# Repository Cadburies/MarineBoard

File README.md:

This project moved into SisuAssistant where the full spec, schematics, and pcb layout are:  https://github.com/Cadburies/SisuAssistant/tree/main/MarineBoard

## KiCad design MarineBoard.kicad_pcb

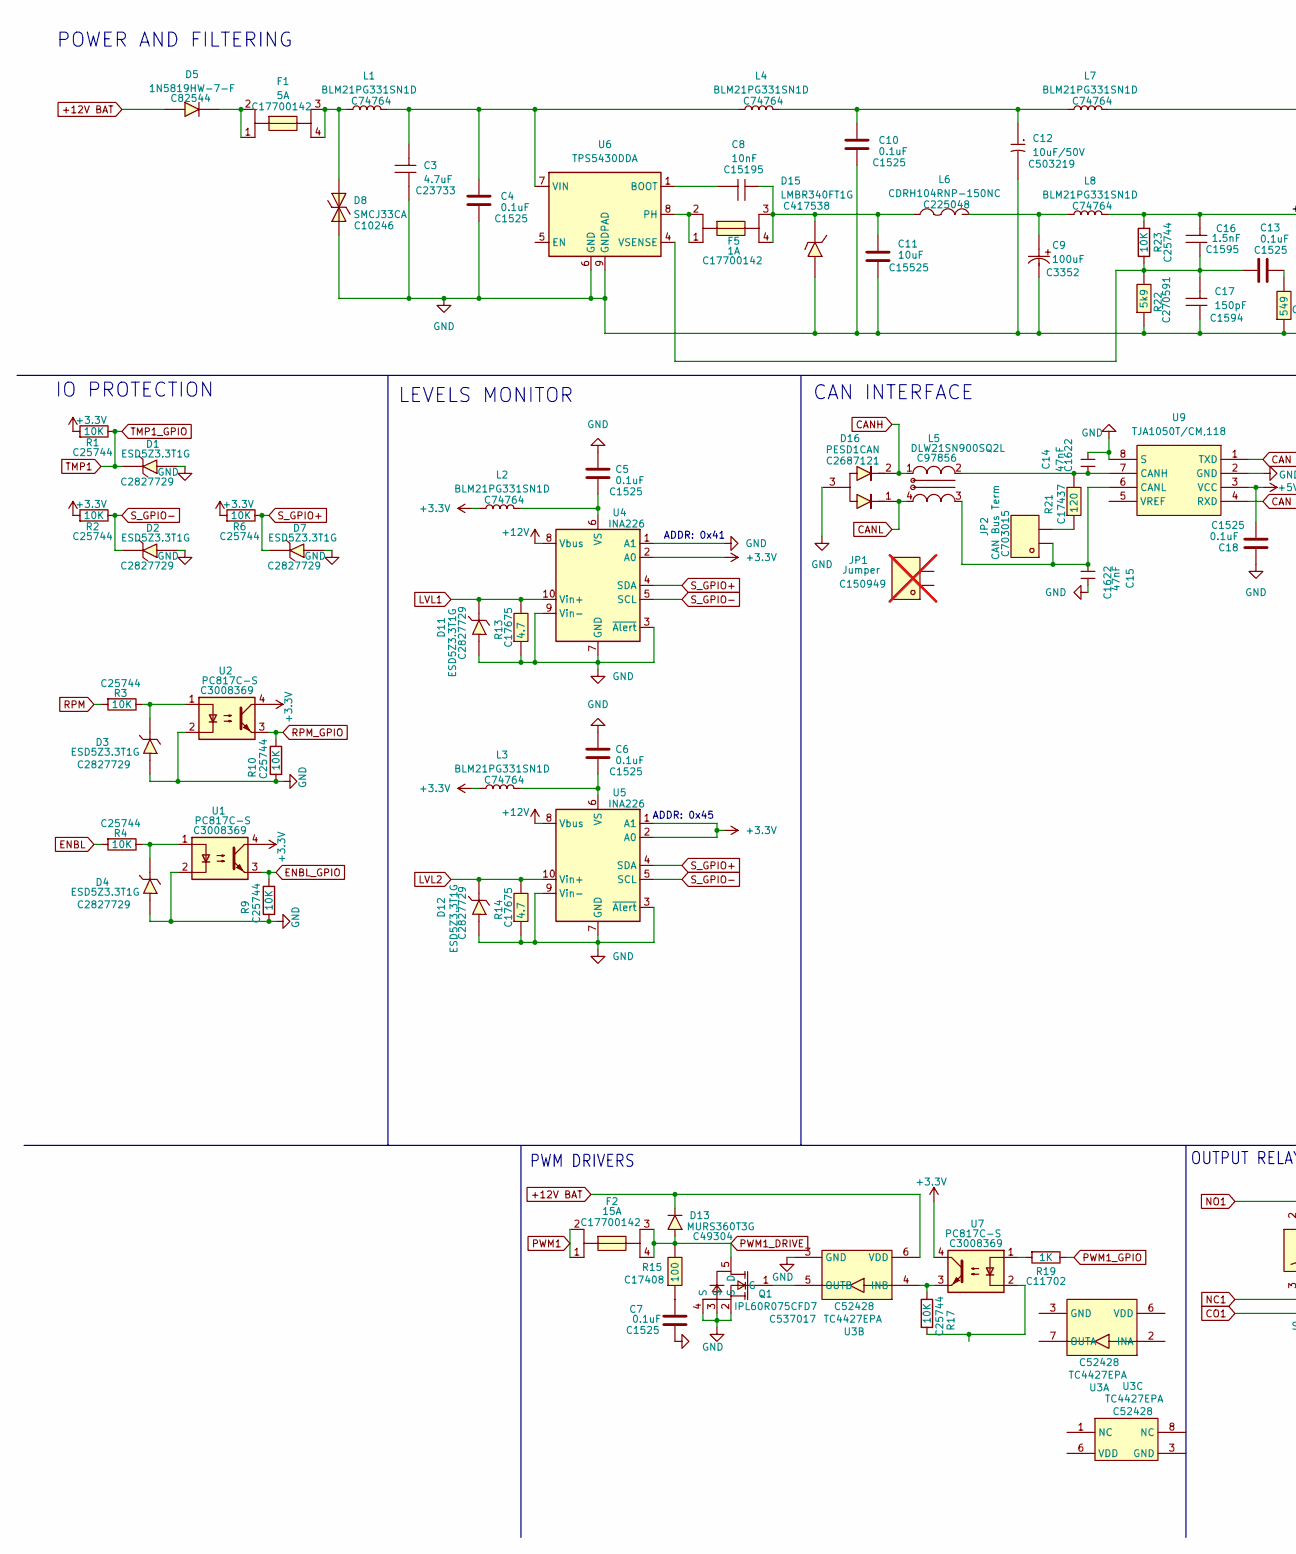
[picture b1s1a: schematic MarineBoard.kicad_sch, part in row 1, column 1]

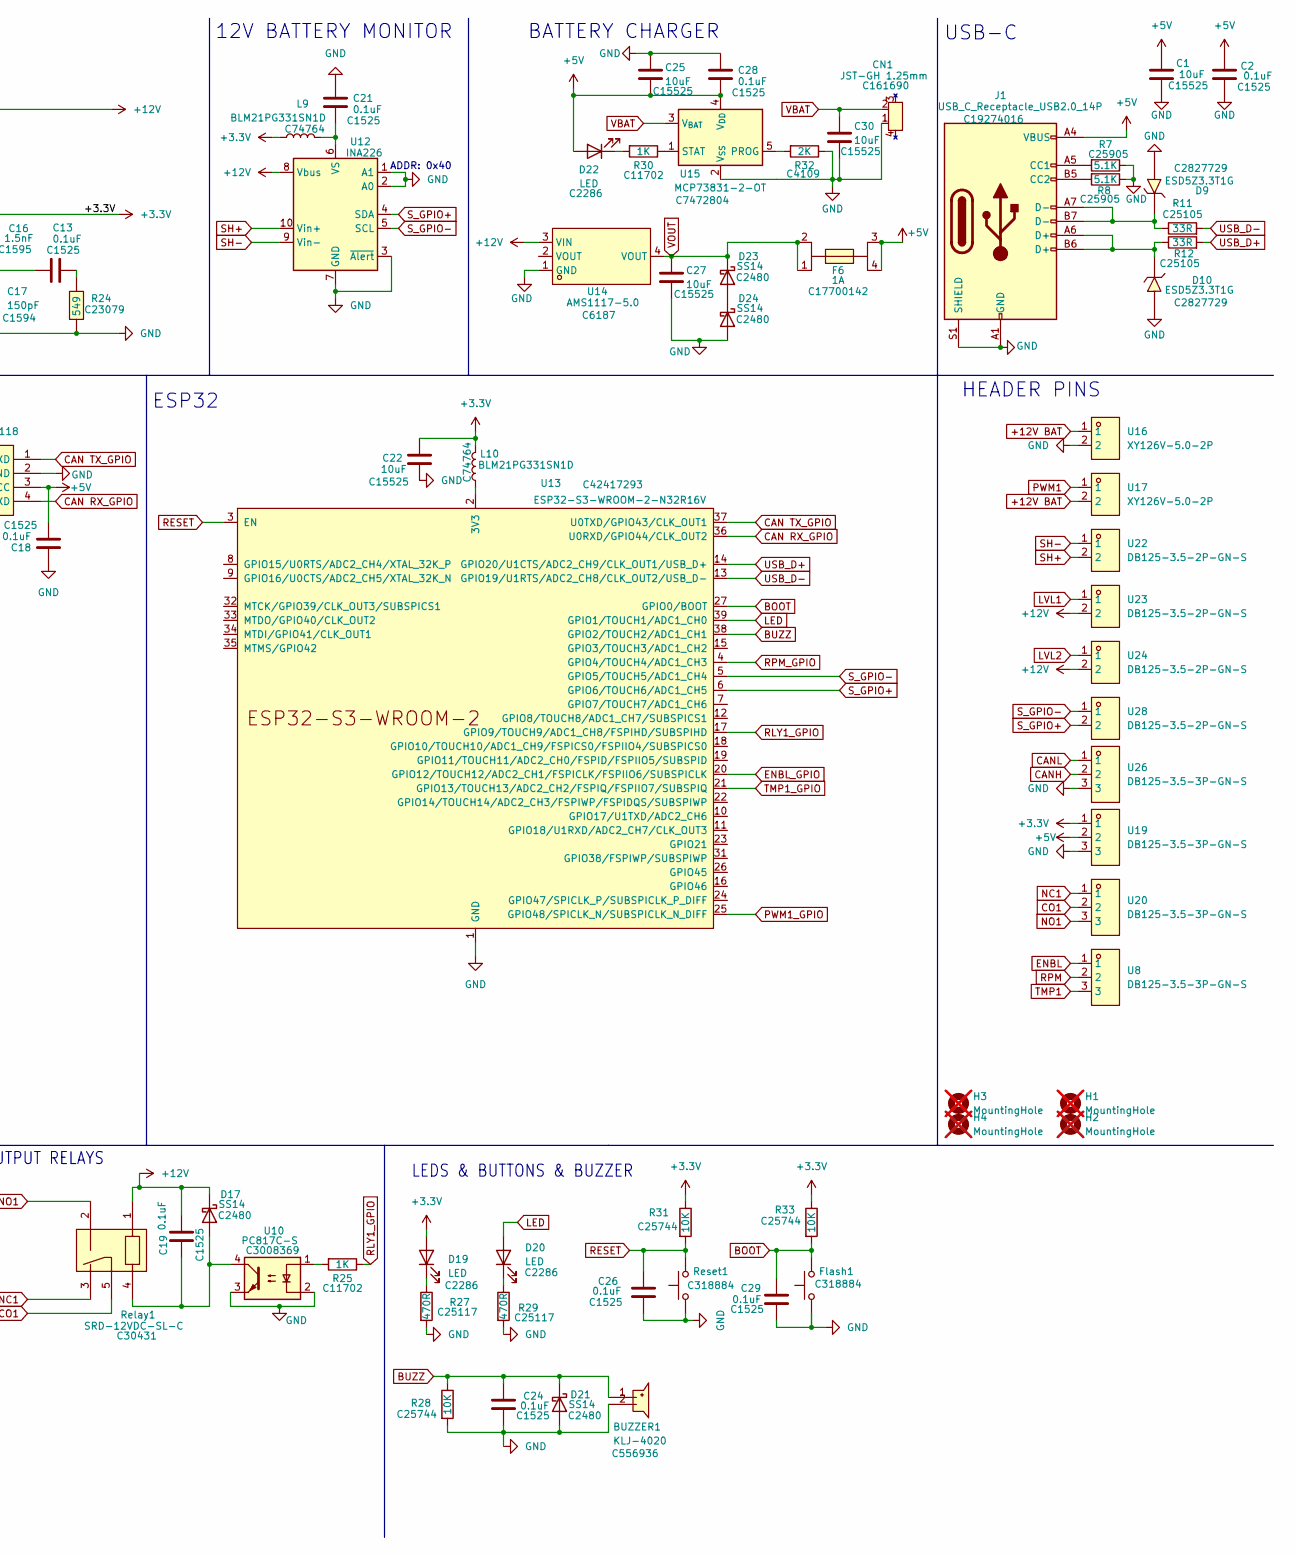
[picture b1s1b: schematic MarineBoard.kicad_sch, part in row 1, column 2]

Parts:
BUZZER1: KLJ-4020; BUZ-SMD_L4.0-W4.0-P3.50-L; LCSC Part C556936
C1, C11, C22, C25, C27, C30: 10uF; C_0402_1005Metric; MNF PART NUMBER C15525; LCSC C15525
C2, C4, C5, C6, C7, C10, C13, C18, C19, C21, C24, C26, C28, C29: 0.1uF; C_0402_1005Metric; MNF PART NUMBER C1525; LCSC C1525
C3: 4.7uF; C0402; LCSC Part C23733
C8: 10nF; C0402; LCSC Part C15195
C9: 100uF; CAP-SMD_BD8.0-L8.3-W8.3-FD; LCSC Part C3352
C12: 10uF/50V; CAP-TH_BD5.0-P2.00-D0.8-FD; LCSC Part C503219
C14, C15: 47nF; C0603; LCSC Part C1622
C16: 1.5nF; C0603; LCSC Part C1595
C17: 150pF; C0603; LCSC Part C1594
CN1: JST-GH 1.25mm; CONN-SMD_2P-P1.25_BM02B-GHS-TBT-LF-SN; LCSC Part C161690
D1, D2, D3, D4, D7, D9, D10, D11, D12: ESD5Z3.3T1G; SOD-523_L1.2-W0.8-LS1.6-FD; LCSC Part C2827729
D5: 1N5819HW-7-F; SOD-123_L2.7-W1.6-LS3.7-RD; LCSC Part C82544
D8: SMCJ33CA; SMC_L6.9-W5.9-LS7.9-BI; LCSC Part C10246
D13: MURS360T3G; SMC_L7.1-W6.2-LS8.1-R-RD; LCSC Part C49304
D15: LMBR340FT1G; SOD-123FL_L2.7-W1.8-LS3.8-RD; LCSC Part C417538
D16: PESD1CAN; SOT-23-3_L2.9-W1.3-P1.90-LS2.4-BL-2; LCSC Part C2687121
D17, D21, D23, D24: SS14; D_SMA; MNF PART NUMBER C2480; LCSC C2480
D19, D20, D22: LED; LED_0603_1608Metric; MNF PART NUMBER C2286; LCSC C2286
F1: 5A; FUSE-SMD_4P-L16.0-W6.7-P9.92; LCSC Part C17700142
F2: 15A; FUSE-SMD_4P-L16.0-W6.7-P9.92; LCSC Part C17700142
F5, F6: 1A; FUSE-SMD_4P-L16.0-W6.7-P9.92; LCSC Part C17700142
Flash1: Flash; SW_Push_1P1T_XKB_TS-1187A; MNF PART NUMBER C318884; LCSC C318884
H1, H2, H3, H4: MountingHole; MountingHole_3.2mm_M3; not fitted
J1: USB_C_Receptacle_USB2.0_14P; USB_C_Receptacle_HCTL_HC-TYPE-C-16P-01A; MNF PART NUMBER C19274016; LCSC C19274016
JP1: Jumper; HDR-TH_2P-P1.27-V-M; LCSC Part C150949; not fitted
JP2: CAN Bus Term; HDR-TH_2P-P1.27-V-M; LCSC Part C703015
L1, L2, L3, L4, L7, L8, L9, L10: BLM21PG331SN1D; L0805; LCSC Part C74764
L5: DLW21SN900SQ2L; FILTER-SMD_4P-L2.0-W1.2-BL_DLW21H; LCSC Part C97856
L6: CDRH104RNP-150NC; IND-SMD_L10.2-W10.0; LCSC Part C225048
Q1: IPL60R075CFD7; VSON-4_L8.1-W8.1-P2.00-BL; LCSC Part C537017
R1, R2, R3, R4, R6, R9, R10, R17, R23, R28, R31, R33: 10K; R_0402_1005Metric; MNF PART NUMBER C25744; LCSC C25744
R7, R8: 5.1K; R_0402_1005Metric; MNF PART NUMBER C25905; LCSC C25905
R11, R12: 33R; R_0402_1005Metric; MNF PART NUMBER C25105; LCSC C25105
R13, R14: 4.7; R0805; LCSC Part C17675
R15: 100; R0805; LCSC Part C17408
R19, R25, R30: 1K; R_0402_1005Metric; MNF PART NUMBER C11702; LCSC C11702
R21: 120; R0805; LCSC Part C17437
R22: 5k9; R0402; LCSC Part C270591
R24: 549; R0603; LCSC Part C23079
R27, R29: 470R; R_0402_1005Metric; MNF PART NUMBER C25117; LCSC C25117
R32: 2K; R_0402_1005Metric; MNF PART NUMBER C4109; LCSC C4109
Relay1: SRD-12VDC-SL-C; RELAY-TH_SRD-XXVDC-XL-C; LCSC Part C30431
Reset1: Reset; SW_Push_1P1T_XKB_TS-1187A; MNF PART NUMBER C318884; LCSC C318884
U1, U2, U7, U10: PC817C-S; SOP-4_L6.5-W4.6-P2.54-LS10.3-TL; LCSC Part C3008369
U3: TC4427EPA; DIP-8_L9.4-W6.4-P2.54-LS9.1-BL; LCSC Part C52428
U4, U5, U12: INA226; VSSOP-10_3x3mm_P0.5mm
U6: TPS5430DDA; TI_SO-PowerPAD-8_ThermalVias
U8, U19, U20, U26: DB125-3.5-3P-GN-S; CONN-TH_3P-P3.50_L7.4-W10.5; LCSC Part C466971
U9: TJA1050T/CM,118; SOIC-8_L5.0-W4.0-P1.27-LS6.0-BL; LCSC Part C6952
U13: ESP32-S3-WROOM-2-N32R16V; ESP32-S3-WROOM-2; MNF PART NUMBER C42417293; LCSC C42417293
U14: AMS1117-5.0; SOT-223_L6.5-W3.5-P2.30-LS7.0-BR; LCSC Part C6187
U15: MCP73831-2-OT; SOT-23-5; MNF PART NUMBER C7472804; LCSC C7472804
U16, U17: XY126V-5.0-2P; CONN-TH_XY126V-5.0-2P; LCSC Part C557646
U22, U23, U24, U28: DB125-3.5-2P-GN-S; CONN-TH_2P-P3.50_L7.4-W7.0; LCSC Part C466970

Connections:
+3.3V: C16.2, C22.1, D19.2 (A), L2.1, L3.1, L8.2, L9.1, L10.2, R1.2, R2.2, R6.2, R23.2, R31.1, R33.1, U1.4, U2.4, U4.2 (A0), U5.1 (A1), U5.2 (A0), U7.4, U19.1
+5V: C1.1, C2.1, C18.2, C25.2, C28.2, D22.2 (A), F6.3, F6.4, J1.A4 (VBUS), J1.A9 (VBUS), J1.B4 (VBUS), J1.B9 (VBUS), U9.3 (VCC), U15.4 (V_{DD}), U19.2
+12V: C19.1, D17.1 (K), L7.2, Relay1.1, U4.8 (Vbus), U5.8 (Vbus), U12.8 (Vbus), U14.3 (VIN), U23.2, U24.2
+12V BAT: D5.2 (A), D13.2 (K), U3.6 (VDD), U16.1, U17.2
BOOT: C29.2, Flash1.2, R33.2, U13.27 (GPIO0/BOOT)
BUZZ: BUZZER1.1 (+), C24.1, D21.1 (K), R28.1, U13.38 (GPIO2/TOUCH2/ADC1_CH1)
CAN RX_GPIO: U9.4 (RXD), U13.36 (U0RXD/GPIO44/CLK_OUT2)
CAN TX_GPIO: U9.1 (TXD), U13.37 (U0TXD/GPIO43/CLK_OUT1)
CANH: D16.2, L5.1, U26.2
CANL: D16.1, L5.4, U26.1
CO1: Relay1.5, U20.2
ENBL: R4.2, U8.1
ENBL_GPIO: R9.1, U1.3, U13.20 (GPIO12/TOUCH12/ADC2_CH1/FSPICLK/FSPIIO6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)
GND: BUZZER1.2 (-), C1.2, C2.2, C3.1, C4.2, C5.1, C6.1, C7.2, C9.2, C10.2, C11.1, C12.2, C14.2, C15.2, C17.1, C18.1, C21.1, C22.2, C24.2, C25.1, C26.1, C27.2, C28.1, C29.1, C30.2, CN1.1, D1.1 (A), D2.1 (A), D3.1 (A), D4.1 (A), D7.1 (A), D8.1 (K), D9.1 (A), D10.1 (A), D11.1 (A), D12.1 (A), D15.2 (A), D16.3, D21.2 (A), D24.2 (A), Flash1.1, J1.A1 (GND), J1.A12 (GND), J1.B1 (GND), J1.B12 (GND), J1.S1 (SHIELD), Q1.2 (S), Q1.3 (S), Q1.4 (S), R7.1, R8.1, R9.2, R10.2, R13.1, R14.1, R22.1, R24.1, R27.2, R28.2, R29.2, R32.1, Reset1.1, U1.2, U2.2, U3.3 (GND), U4.1 (A1), U4.3 (~Alert), U4.7 (GND), U4.9 (Vin-), U5.3 (~Alert), U5.7 (GND), U5.9 (Vin-), U6.6 (GND), U6.9 (GNDPAD), U9.2 (GND), U9.8 (S), U10.2, U10.3, U12.1 (A1), U12.2 (A0), U12.3 (~Alert), U12.7 (GND), U13.1 (GND), U13.40 (GND), U13.41 (GND), U14.1 (GND), U15.2 (V_{SS}), U16.2, U19.3, U26.3
LED: D20.2 (A), U13.39 (GPIO1/TOUCH1/ADC1_CH0)
LVL1: D11.2 (K), R13.2, U4.10 (Vin+), U23.1
LVL2: D12.2 (K), R14.2, U5.10 (Vin+), U24.1
NC1: Relay1.3, U20.1
NO1: Relay1.2, U20.3
unnamed: C7.1, R15.1
unnamed: C9.1, L6.2, L8.1
unnamed: C10.1, C12.1, L4.2, L7.1
unnamed: C13.2, R24.2
unnamed: D3.2 (K), R3.1, U2.1
unnamed: D4.2 (K), R4.1, U1.1
unnamed: D5.1 (K), F1.1, F1.2
unnamed: D8.2 (A), F1.3, F1.4, L1.1
unnamed: D9.2 (K), J1.A7 (D-), J1.B7 (D-), R11.1
unnamed: D10.2 (K), J1.A6 (D+), J1.B6 (D+), R12.1
unnamed: C8.1, C11.2, D15.1 (C), F5.3, F5.4, L6.1
unnamed: C19.2, D17.2 (A), Relay1.4, U10.4
unnamed: D19.1 (K), R27.1
unnamed: D20.1 (K), R29.1
unnamed: D22.1 (K), R30.2
unnamed: D23.2 (A), D24.1 (K)
unnamed: J1.A5 (CC1), R7.2
unnamed: J1.B5 (CC2), R8.2
unnamed: JP2.2, R21.1
unnamed: Q1.1 (G), U3.5 (OUTB)
unnamed: R17.2, U7.2
unnamed: R19.2, U7.1
unnamed: R25.2, U10.1
unnamed: R17.1, U3.4 (INB), U7.3
unnamed: C5.2, L2.2, U4.6 (VS)
unnamed: C6.2, L3.2, U5.6 (VS)
unnamed: C8.2, U6.1 (BOOT)
unnamed: F5.1, F5.2, U6.8 (PH)
unnamed: C3.2, C4.1, L1.2, L4.1, U6.7 (VIN)
unnamed: C13.1, C16.1, C17.2, R22.2, R23.1, U6.4 (VSENSE)
unnamed: C14.1, L5.2, R21.2, U9.7 (CANH)
unnamed: C15.1, JP2.1, L5.3, U9.6 (CANL)
unnamed: C21.2, L9.2, U12.6 (VS)
unnamed: L10.1, U13.2 (3V3)
unnamed: R32.2, U15.5 (PROG)
unnamed: R30.1, U15.1 (STAT)
PWM1: F2.1, F2.2, U17.1
PWM1_DRIVE: D13.1 (A), F2.3, F2.4, Q1.5 (D), R15.2
PWM1_GPIO: R19.1, U13.25 (GPIO48/SPICLK_N/SUBSPICLK_N_DIFF)
RESET: C26.2, R31.2, Reset1.2, U13.3 (EN)
RLY1_GPIO: R25.1, U13.17 (GPIO9/TOUCH9/ADC1_CH8/FSPIHD/SUBSPIHD)
RPM: R3.2, U8.2
RPM_GPIO: R10.1, U2.3, U13.4 (GPIO4/TOUCH4/ADC1_CH3)
SH+: U12.10 (Vin+), U22.2
SH-: U12.9 (Vin-), U22.1
S_GPIO+: D7.2 (K), R6.1, U4.4 (SDA), U5.4 (SDA), U12.4 (SDA), U13.6 (GPIO6/TOUCH6/ADC1_CH5), U28.2
S_GPIO-: D2.2 (K), R2.1, U4.5 (SCL), U5.5 (SCL), U12.5 (SCL), U13.5 (GPIO5/TOUCH5/ADC1_CH4), U28.1
TMP1: D1.2 (K), R1.1, U8.3, U13.21 (GPIO13/TOUCH13/ADC2_CH2/FSPIQ/FSPIIO7/S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)
USB_D+: R12.2, U13.14 (GPIO20/U1CTS/ADC2_CH9/CLK_OUT1/USB_D+)
USB_D-: R11.2, U13.13 (GPIO19/U1RTS/ADC2_CH8/CLK_OUT2/USB_D-)
VBAT: C30.1, CN1.2, U15.3 (V_{BAT})
VOUT: C27.1, D23.1 (K), F6.1, F6.2, U14.4 (VOUT)

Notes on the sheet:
BATTERY CHARGER
IO PROTECTION
LEDS & BUTTONS & BUZZER
ESP32
HEADER PINS
OUTPUT RELAYS
ADDR: 0x45
ADDR: 0x40
LEVELS MONITOR
CAN INTERFACE
PWM DRIVERS
ADDR: 0x41
POWER AND FILTERING
12V BATTERY MONITOR
USB-C

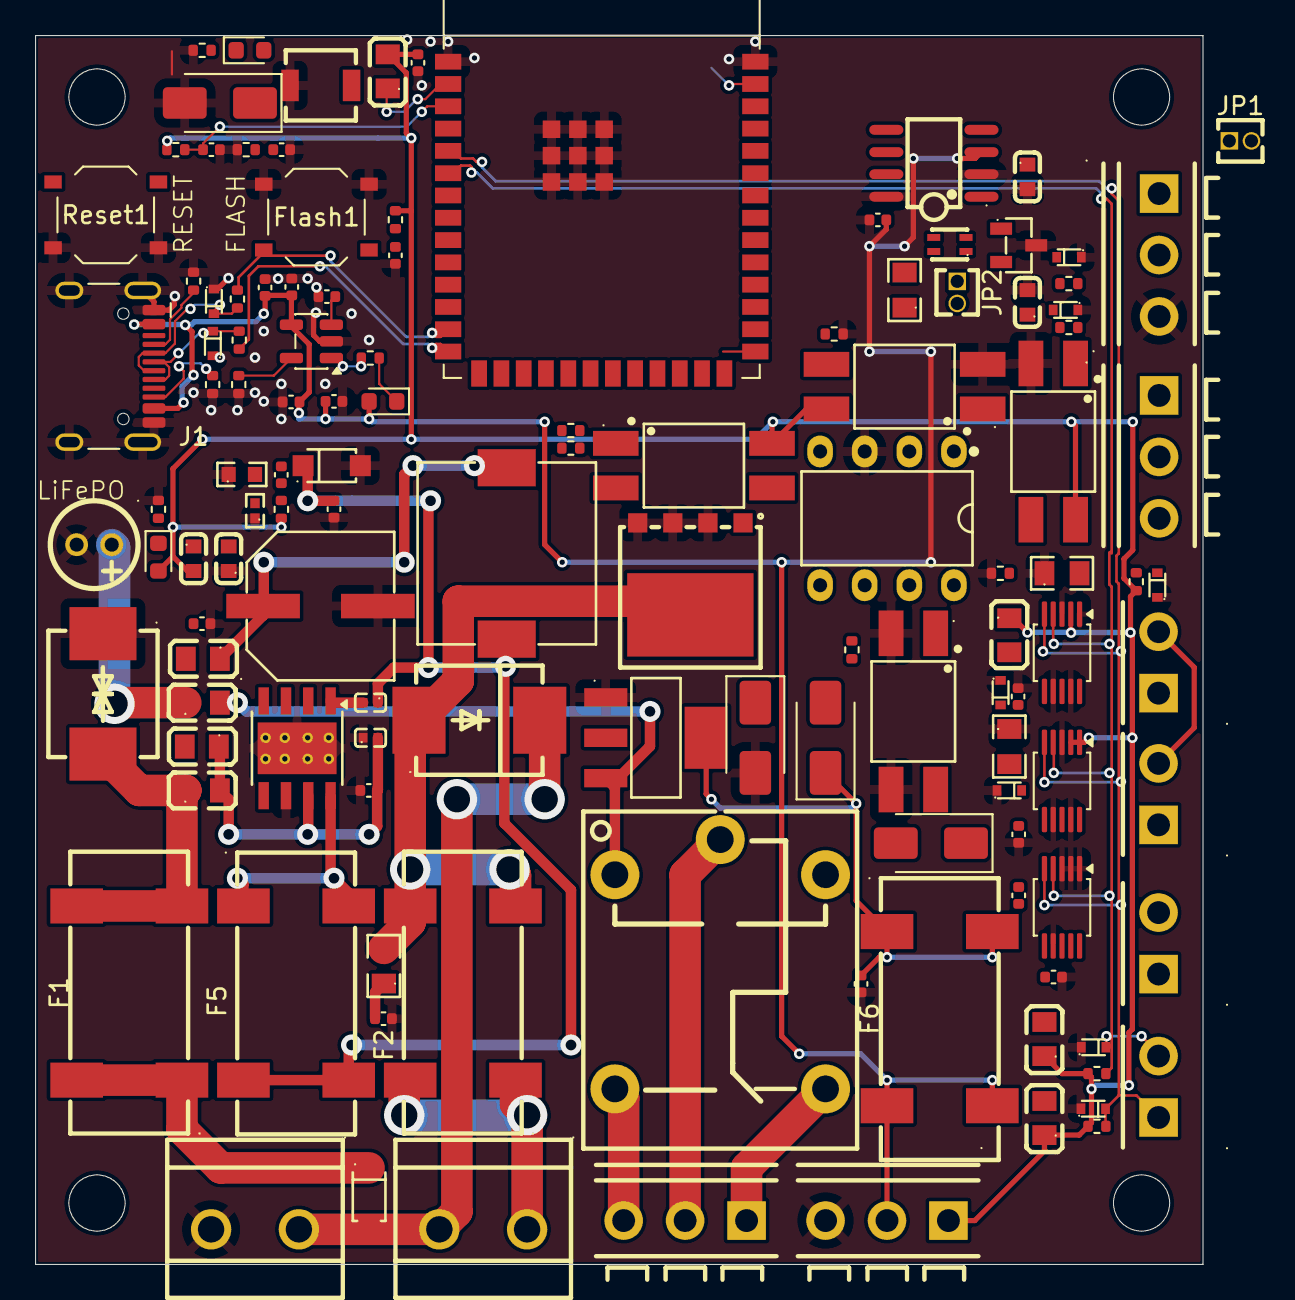
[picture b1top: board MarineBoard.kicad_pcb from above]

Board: 2 copper layers, 66.5 x 70.0 mm, 127 parts (1 on the bottom side), 71 nets.

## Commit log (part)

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2026-03-23 Initial commit of MarineBoard project
